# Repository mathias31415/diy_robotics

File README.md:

# diy_robotics

## Table of Contents
1. [Video of the results](#video)
2. [Overview](#overview)
3. [Possible improvements](#improvements)
4. [Part list](#partlist)
5. [Assembly-Videos by pfuscher666](#assemblyvideos)

<a name="video"/>

## Video of the results (in German)

This [YouTube video](https://www.youtube.com/watch?v=qf8R6U7XTOY) shows the results of our project work:

<a name="overview"/>

## Overview

This repo contains the results of a project work at the University of Applied Sciences Karlsruhe by **Robin Wolf, Hannes Bornemann and Mathias Fuhrer**. As part of the project work, the [Six-Axis Robot Arm WE-R2.4 from LoboCNC](https://www.printables.com/de/model/132260-we-r24-six-axis-robot-arm) was set up and a new gripper was developed.

The project was supervised by Gergely Sóti, Philipp Augenstein and Prof. Dr.-Ing. habil. Björn Hein.

The CAD files of the gripper and assembly instructions can be found in folder [diy_robotics_gripper_cad](https://github.com/mathias31415/diy_robotics/tree/main/diy_robotics_gripper_cad).

Two PCBs were designed for the electrical wiring: one PCB for the 6 axes and one PCB for the gripper. The KiCAD and Gerber files can be found in the folders [diy_robotics_arm_pcb](https://github.com/mathias31415/diy_robotics/tree/main/diy_robotics_arm_pcb) and [diy_robotics_gripper_pcb](https://github.com/mathias31415/diy_robotics/tree/main/diy_robotics_gripper_pcb).

To control the 6 axes and the gripper, ROS2 implementations were written that communicate via Wifi with an ESP32, from which the axes and the gripper are then moved. One ESP32 is responsible for the 6 axes, and the second ESP32 is responsible for the gripper.

The ROS2 packages are packaged in Docker containers so that they can be used by others without any problems. The repos of our ROS2 packages are linked in the folder [ROS-Packages](https://github.com/mathias31415/diy_robotics/tree/main/ROS-Packages). To just use our ROS application go to the repo [diy_robot_application](https://github.com/RobinWolf/diy_robot_application) and follow the HowTo. To understand our implementation you should read all readmes of our ROS repos 

The PC on which the ROS2 packages are executed must be connected to the same Wifi as the two ESP32s. The two ESP32s then receive messages from the PC via TCP-IP with the commands for the gripper and the 6-axes and then control the gripper and the axes accordingly. The VS-Code PlatformIO project folders for the ESP32 of the gripper and the axes can be found in the folders [diy_robotics_arm_esp32](https://github.com/mathias31415/diy_robotics/tree/main/diy_robotics_arm_esp32) and [diy_robotics_gripper_esp32](https://github.com/mathias31415/diy_robotics/tree/main/diy_robotics_gripper_esp32). Make sure to adapt the SSID and IP address as well as the password of your Wifi in the ``Configuration.h`` files.

The [hardwaretest_without_ROS](https://github.com/mathias31415/diy_robotics/tree/main/hardwaretest_without_ROS) folder contains additional programs to test the hardware without ROS via the Serial Monitor.

<a name="improvements"/>

## Possible improvements

- Conversion of the robot to metric screws
- Endstops or sensors to determine the position of the robot or to move it to a home position

<a name="partlist"/>

## Part list (as of March 2024)
The information serves as a guide only. Prices may change over time. It is also worth comparing other providers and manufacturers.
(Parts such as screws, filament and glue are not listed)

### 1. Robot-arm
| Index | Description | Quantity | Total price in € | Link |
| --- | --- | --- | --- | --- |
| 1 | Nema 17 Stepper-Motor 42Ncm | 3 | 15,55 | [Link](https://www.omc-stepperonline.com/de/3-stueck-e-serie-nema-17-bipolar-42-ncm-59-49-oz-in-1-5a-42x42x38mm-4-draehte-3-17he15-1504s) |
| 2 | Minibea PM35L-048 Stepper-Motor | 3 | 18,20 | [Link](https://www.ebay.de/itm/403845575203?_trkparms=amclksrc%3DITM%26aid%3D777008%26algo%3DPERSONAL.TOPIC%26ao%3D1%26asc%3D20230811123857%26meid%3D01b980ffd3f64d67a8210c3d282fd210%26pid%3D101770%26rk%3D1%26rkt%3D1%26itm%3D403845575203%26pmt%3D1%26noa%3D1%26pg%3D4375194%26algv%3DRecentlyViewedItemsV2%26brand%3DMarkenlos&_trksid=p4375194.c101770.m146925&_trkparms=parentrq%3Acd81805118b0a8cc93d6ff8cffffc172%7Cpageci%3Aa6388820-82dd-11ee-97f3-8e07020e1f61%7Ciid%3A1%7Cvlpname%3Avlp_homepage) |
| 3 | 6mm steel balls for bearings | 200 | 9,99 | [Link](https://www.amazon.de/dp/B01LPZ56ZC?psc=1&ref=ppx_yo2ov_dt_b_product_details ) |
| 4 | additional connection cable for motors 1,5m | 6 | 9,59 | [Link](https://www.amazon.de/Iverntech-Schrittmotor-Terminal-3D-Drucker-Stepper/dp/B08SQ35LRQ/ref=sr_1_6?crid=2UUMN13RQ0TTT&keywords=stepper%2Bmotor%2Bkabel&qid=1700576677&sprefix=stepper%2Bmotor%2B%2Caps%2C149&sr=8-6&th=1 ) |
| 5 | Power supply 24V 350W | 1 | 22,97 | [Link](https://www.omc-stepperonline.com/de/lrs-350-24-mean-well-350w-24vdc-14-6a-115-230vac-geschlossenes-schaltnetzteil-lrs-350-24) |
| 6 | Step-Down Converter 24V - 5V | 2 | 4,00 | [Link](https://www.amazon.de/Yizhet-Converter-Spannungsregler-Einstellbares-Abw%C3%A4Rtsmodul/dp/B0CKWYXD89/ref=sr_1_2_sspa?keywords=step+down+modul&qid=1699960183&sr=8-2-spons&sp_csd=d2lkZ2V0TmFtZT1zcF9hdGY&psc=1) |

### 2. Gripper
| Index | Description | Quantity | Total price in € | Link |
| --- | --- | --- | --- | --- |
| 1 | Servo SG90 Continuous Drive (Metal 360 Degree) | 2 | 9,00 | [Link](https://de.aliexpress.com/item/1005004550512467.html?spm=a2g0o.order_list.order_list_main.10.12875c5fjUap8p&gatewayAdapt=glo2deu) |

### 3. PCBs
The geber-files for the PCBs can be found in folders [diy_robotics_arm_pcb](https://github.com/mathias31415/diy_robotics/tree/main/diy_robotics_arm_pcb) and [diy_robotics_gripper_pcb](https://github.com/mathias31415/diy_robotics/tree/main/diy_robotics_gripper_pcb). With the geber-files, the PCBs can be ordered from any manufacturer. At JLCPCB we paid a total of just over €30 for 5 pieces of both PCBs.
The parts for assembling the PCBs are listed below. Note that some parts are required for both PCBs and are therefore listed twice. However, one set is often sufficient for both PCBs (e.g. for the pin headers). For components such as the ESP-32, it is cheaper to buy a set of two for both PCBs than to order two individual ESP-32s.

#### 3.1 Arm PCB
| Index | Description | Quantity | Total price in € | Link |
| --- | --- | --- | --- | --- |
| 1 | 0.96 Inch OLED Display SSD1306 | 1 | 1,78 | [Link](https://de.aliexpress.com/item/1005005970901119.html?spm=a2g0o.order_list.order_list_main.22.4a065c5ffRtZfv&gatewayAdapt=glo2deu) |
| 2 | ESP-32 | 1 | 10,00 | [Link](https://www.amazon.de/gp/aw/d/B074RG86SR/?_encoding=UTF8&pd_rd_plhdr=t&aaxitk=6a9e09b157f2b15a9cc364c1aba715aa&hsa_cr_id=4742246160502&qid=1699959775&sr=1-1-e0fa1fdd-d857-4087-adda-5bd576b25987&ref_=sbx_be_s_sparkle_mcd_asin_0_title&pd_rd_w=ee0VR&content-id=amzn1.sym.6f8b36f0-c2c9-44f2-97a8-5b151d2fc9c7%3Aamzn1.sym.6f8b36f0-c2c9-44f2-97a8-5b151d2fc9c7&pf_rd_p=6f8b36f0-c2c9-44f2-97a8-5b151d2fc9c7&pf_rd_r=0TBV9VYJCQK5QB253DBZ&pd_rd_wg=KZCjO&pd_rd_r=297525bc-30e7-47c9-996a-8a255adffee4)  |
| 3 | 2-Pin Screw Terminal 5mm | 3 | 4,56 for a set | [Link](https://de.aliexpress.com/item/1005005595075178.html?spm=a2g0o.order_list.order_list_main.17.4a065c5ffRtZfv&gatewayAdapt=glo2deu) |
| 4 | Pin Header 1x4 Pin Male 2,54mm | 6 |1,77 for male + female set | [Link](https://de.aliexpress.com/item/4000873858801.html?spm=a2g0o.detail.pcDetailTopMoreOtherSeller.2.e4a5600cBKuomq&gps-id=pcDetailTopMoreOtherSeller&scm=1007.40050.354490.0&scm_id=1007.40050.354490.0&scm-url=1007.40050.354490.0&pvid=c41c94ec-099f-42bf-a647-59697bc6a5d5&_t=gps-id:pcDetailTopMoreOtherSeller,scm-url:1007.40050.354490.0,pvid:c41c94ec-099f-42bf-a647-59697bc6a5d5,tpp_buckets:668%232846%238114%231999&pdp_npi=4%40dis%21EUR%211.77%211.77%21%21%211.89%211.89%21%4021038dfc17098923902746506e96e7%2110000010058190554%21rec%21DE%213958237401%21&utparam-url=scene%3ApcDetailTopMoreOtherSeller%7Cquery_from%3A) |
| 5 | Capacitor 25V 100uF | 6 | 1,78 for 50pcs | [Link](https://de.aliexpress.com/item/1005005945738204.html?spm=a2g0o.order_list.order_list_main.11.4a065c5ffRtZfv&gatewayAdapt=glo2deu) |
| 6 | DRV8825 Stepper Driver | 6 | 10,00 |  [Link](https://www.amazon.de/dp/B07YFS29W7?psc=1&ref=ppx_yo2ov_dt_b_product_details ) |
| 7 | 4-way DIP-Switch 2,54mm | 6 | 1,86 for 10pcs | [Link](https://de.aliexpress.com/item/1005006109195564.html?spm=a2g0o.order_list.order_list_main.10.4a065c5ffRtZfv&gatewayAdapt=glo2deu) |
| 8 | Female pin header 2,54mm for the display, ESP-32 and Stepper Drivers |  | 1,77 for male + female set | [Link](https://de.aliexpress.com/item/4000873858801.html?spm=a2g0o.detail.pcDetailTopMoreOtherSeller.2.e4a5600cBKuomq&gps-id=pcDetailTopMoreOtherSeller&scm=1007.40050.354490.0&scm_id=1007.40050.354490.0&scm-url=1007.40050.354490.0&pvid=c41c94ec-099f-42bf-a647-59697bc6a5d5&_t=gps-id:pcDetailTopMoreOtherSeller,scm-url:1007.40050.354490.0,pvid:c41c94ec-099f-42bf-a647-59697bc6a5d5,tpp_buckets:668%232846%238114%231999&pdp_npi=4%40dis%21EUR%211.77%211.77%21%21%211.89%211.89%21%4021038dfc17098923902746506e96e7%2110000010058190554%21rec%21DE%213958237401%21&utparam-url=scene%3ApcDetailTopMoreOtherSeller%7Cquery_from%3A) |

#### 3.2 Gripper PCB
| Index | Description | Quantity | Total price in € | Link |
| --- | --- | --- | --- | --- |
| 1 | 0.96 Inch OLED Display SSD1306 | 1 | 1,78 | [Link](https://de.aliexpress.com/item/1005005970901119.html?spm=a2g0o.order_list.order_list_main.22.4a065c5ffRtZfv&gatewayAdapt=glo2deu) |
| 2 | ESP-32 | 1 | 10,00 | [Link](https://www.amazon.de/gp/aw/d/B074RG86SR/?_encoding=UTF8&pd_rd_plhdr=t&aaxitk=6a9e09b157f2b15a9cc364c1aba715aa&hsa_cr_id=4742246160502&qid=1699959775&sr=1-1-e0fa1fdd-d857-4087-adda-5bd576b25987&ref_=sbx_be_s_sparkle_mcd_asin_0_title&pd_rd_w=ee0VR&content-id=amzn1.sym.6f8b36f0-c2c9-44f2-97a8-5b151d2fc9c7%3Aamzn1.sym.6f8b36f0-c2c9-44f2-97a8-5b151d2fc9c7&pf_rd_p=6f8b36f0-c2c9-44f2-97a8-5b151d2fc9c7&pf_rd_r=0TBV9VYJCQK5QB253DBZ&pd_rd_wg=KZCjO&pd_rd_r=297525bc-30e7-47c9-996a-8a255adffee4) |
| 3 | 2-Pin Screw Terminal 5mm | 2 | 4,56 for a set | [Link](https://de.aliexpress.com/item/1005005595075178.html?spm=a2g0o.order_list.order_list_main.17.4a065c5ffRtZfv&gatewayAdapt=glo2deu) |
| 4 | Pin Header 1x4 Pin Male 2,54mm | 1 | 1,77 for male + female set | [Link](https://de.aliexpress.com/item/4000873858801.html?spm=a2g0o.detail.pcDetailTopMoreOtherSeller.2.e4a5600cBKuomq&gps-id=pcDetailTopMoreOtherSeller&scm=1007.40050.354490.0&scm_id=1007.40050.354490.0&scm-url=1007.40050.354490.0&pvid=c41c94ec-099f-42bf-a647-59697bc6a5d5&_t=gps-id:pcDetailTopMoreOtherSeller,scm-url:1007.40050.354490.0,pvid:c41c94ec-099f-42bf-a647-59697bc6a5d5,tpp_buckets:668%232846%238114%231999&pdp_npi=4%40dis%21EUR%211.77%211.77%21%21%211.89%211.89%21%4021038dfc17098923902746506e96e7%2110000010058190554%21rec%21DE%213958237401%21&utparam-url=scene%3ApcDetailTopMoreOtherSeller%7Cquery_from%3A) |
| 5 | Female pin header 2,54mm for the display, ESP-32 and Stepper Drivers |  |1,77 for male + female set | [Link](https://de.aliexpress.com/item/4000873858801.html?spm=a2g0o.detail.pcDetailTopMoreOtherSeller.2.e4a5600cBKuomq&gps-id=pcDetailTopMoreOtherSeller&scm=1007.40050.354490.0&scm_id=1007.40050.354490.0&scm-url=1007.40050.354490.0&pvid=c41c94ec-099f-42bf-a647-59697bc6a5d5&_t=gps-id:pcDetailTopMoreOtherSeller,scm-url:1007.40050.354490.0,pvid:c41c94ec-099f-42bf-a647-59697bc6a5d5,tpp_buckets:668%232846%238114%231999&pdp_npi=4%40dis%21EUR%211.77%211.77%21%21%211.89%211.89%21%4021038dfc17098923902746506e96e7%2110000010058190554%21rec%21DE%213958237401%21&utparam-url=scene%3ApcDetailTopMoreOtherSeller%7Cquery_from%3A) |

<a name="assemblyvideos"/>

## Assembly-Videos by pfuscher666

[Pfuscher666](https://www.youtube.com/@pfuscher666) made a nice assembly video series on YouTube using our Github repo. If you want to recreate the robot, we recommend checking out his [playlist](https://youtube.com/playlist?list=PLlPSE-8AfOheRNZ__qo-JLWLydIsqo4Fw&si=UZEIlQIDYb_gISjW).

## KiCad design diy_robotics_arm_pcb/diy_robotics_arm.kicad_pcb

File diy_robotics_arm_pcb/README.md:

# diy_robotics_arm_pcb

① 0.96 Inch OLED Display SSD1306 (1 pcs.) 

② ESP-32 (1 pcs.)

③ 2-Pin Screw Terminal 5mm (3 pcs.)

④ Pin Header 1x4 Pin Male 2,54mm (6 pcs.)

⑤ Capacitor 25V 100uF (6 pcs.)

⑥ DRV8825 Stepper Driver (6 pcs.)

⑦ 4-way DIP-Switch 2,54mm (6 pcs.)

(①, ② and  ⑥ are plugged into female pin header 2,54mm)

5V for the ESP32 power supply must be connected to the "VCC_ESP32" screw terminal. 24V for the servo stepper power supply must be connected to the "VCC_Stepper" (on the picture incorrectly "VCC_Servo") screw terminal. The steppers of axes 1 - 6 are connected to the pin header "Axis 1-6". An external enable switch can be connected to the "Enable" screw terminal. This allows the axes to be switched off independently of the software. If no switch is to be used, the contacts can be short-circuited.

### Schamatic

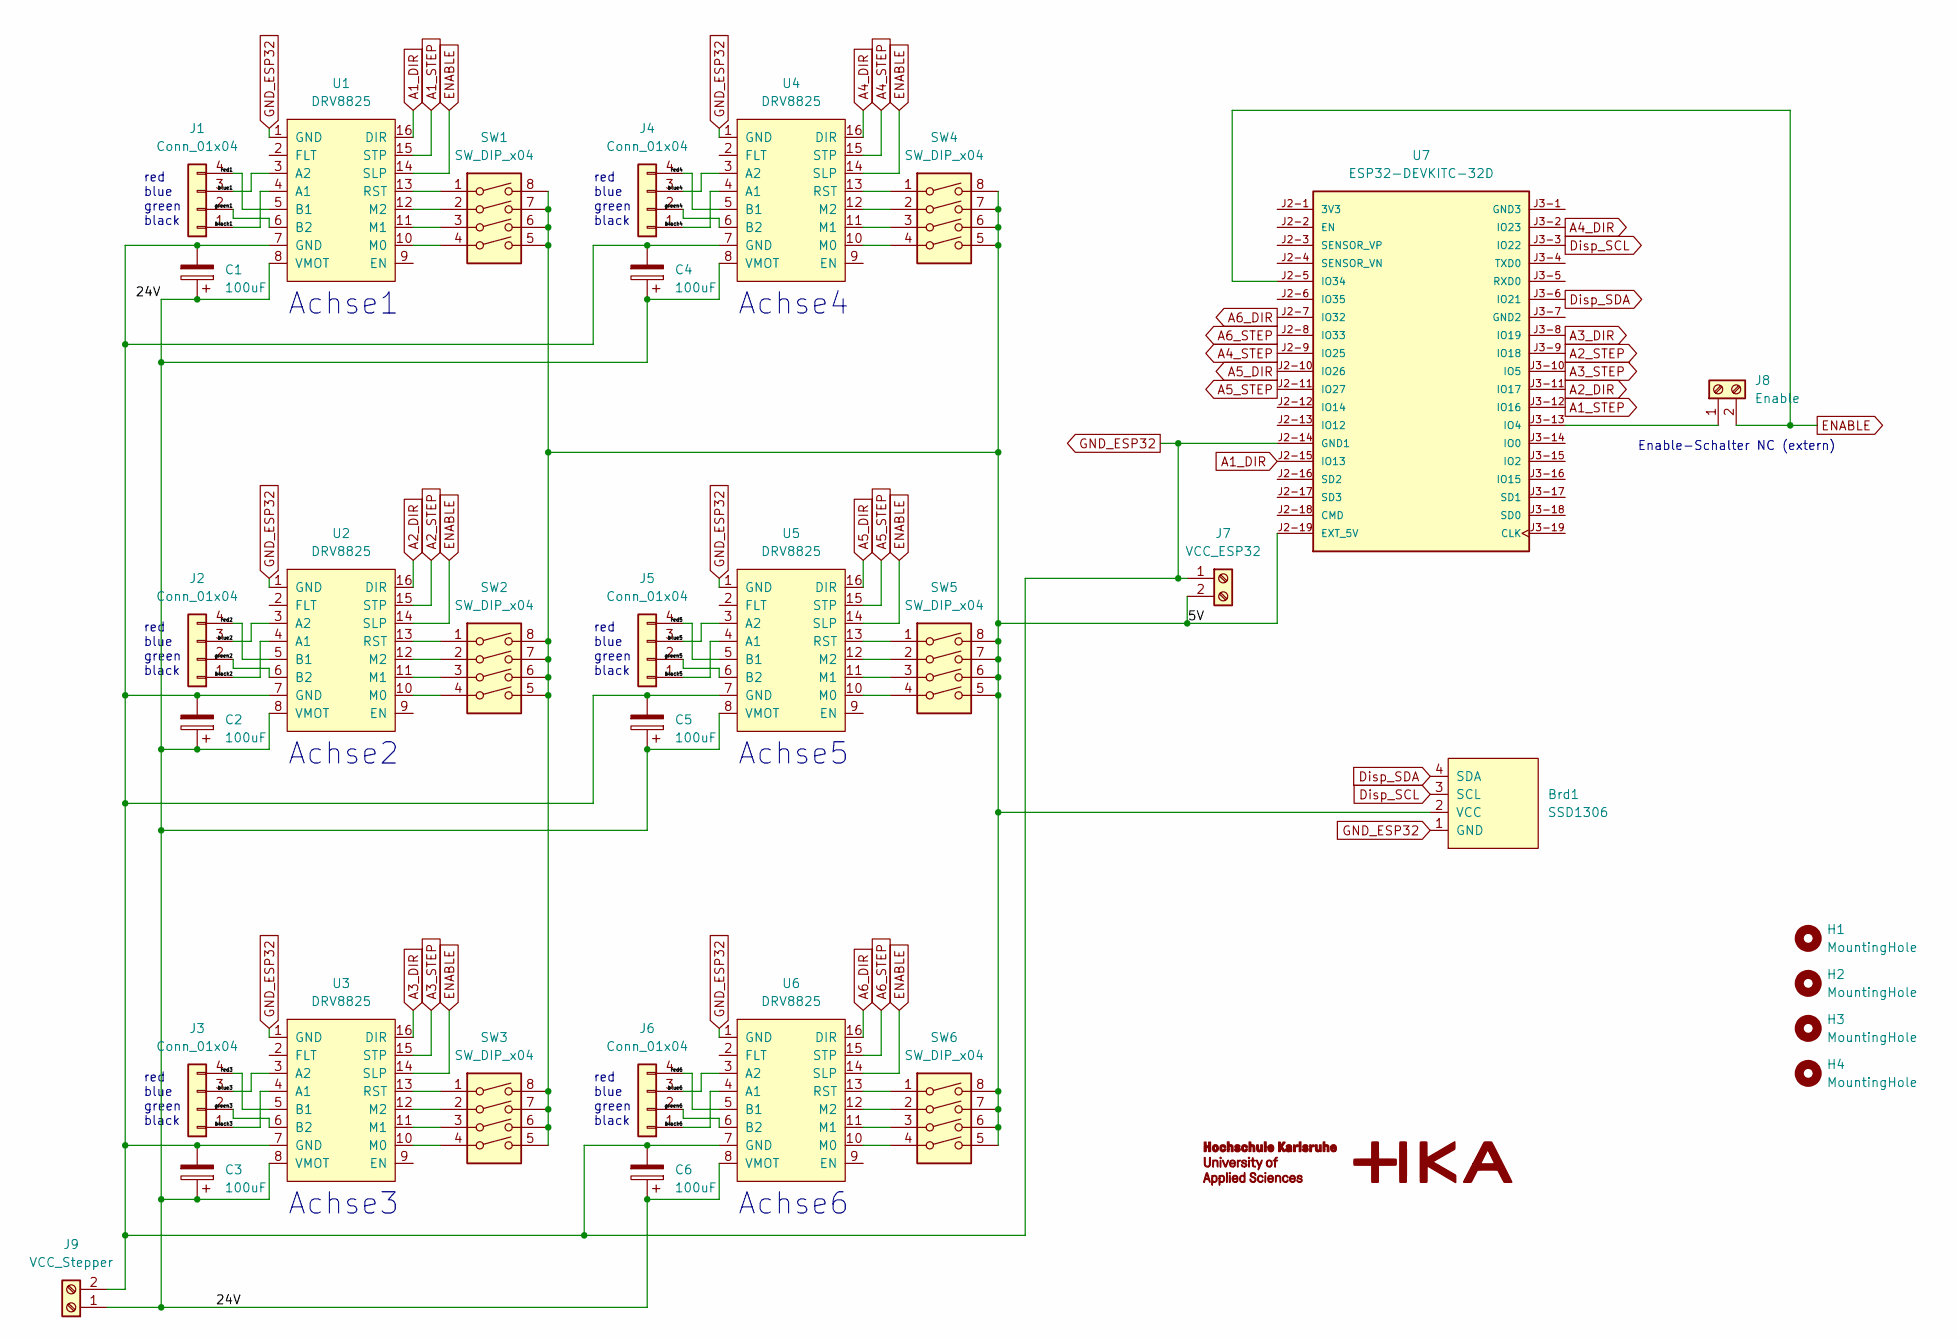
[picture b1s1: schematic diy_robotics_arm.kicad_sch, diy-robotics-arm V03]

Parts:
Brd1: SSD1306; 128x64OLED
C1, C2, C3, C4, C5, C6: 100uF; CP_Radial_D5.0mm_P2.00mm
H1, H2, H3, H4: MountingHole; MountingHole_3.2mm_M3_DIN965_Pad
J1, J2, J3, J4, J5, J6: Conn_01x04; PinHeader_1x04_P2.54mm_Vertical
J7: VCC_ESP32; TerminalBlock_Phoenix_MKDS-1,5-2_1x02_P5.00mm_Horizontal
J8: Enable; TerminalBlock_Phoenix_MKDS-1,5-2_1x02_P5.00mm_Horizontal
J9: VCC_Stepper; TerminalBlock_Phoenix_MKDS-1,5-2_1x02_P5.00mm_Horizontal
SW1, SW2, SW3, SW4, SW5, SW6: SW_DIP_x04; SW_DIP_SPSTx04_Slide_9.78x12.34mm_W7.62mm_P2.54mm
U1, U2, U3, U4, U5, U6: DRV8825; DRV8825_Breakout_15.2x20.3mm
U7: ESP32-DEVKITC-32D; MODULE_ESP32-DEVKITC-32D; PARTREV V4

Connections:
/5V: Brd1.2 (VCC), J7.2, SW1.5, SW1.6, SW1.7, SW1.8, SW2.5, SW2.6, SW2.7, SW2.8, SW3.5, SW3.6, SW3.7, SW3.8, SW4.5, SW4.6, SW4.7, SW4.8, SW5.5, SW5.6, SW5.7, SW5.8, SW6.5, SW6.6, SW6.7, SW6.8, U7.J2-19 (EXT_5V)
/24V: C1.1, C2.1, C3.1, C4.1, C5.1, C6.1, J9.1, U1.8 (VMOT), U2.8 (VMOT), U3.8 (VMOT), U4.8 (VMOT), U5.8 (VMOT), U6.8 (VMOT)
/black1: J1.1, U1.4 (A1)
/black2: J2.1, U2.4 (A1)
/black3: J3.1, U3.4 (A1)
/black4: J4.1, U4.4 (A1)
/black5: J5.1, U5.4 (A1)
/black6: J6.1, U6.4 (A1)
/blue1: J1.3, U1.3 (A2)
/blue2: J2.3, U2.3 (A2)
/blue3: J3.3, U3.3 (A2)
/blue4: J4.3, U4.3 (A2)
/blue5: J5.3, U5.3 (A2)
/blue6: J6.3, U6.3 (A2)
/green1: J1.2, U1.6 (B2)
/green2: J2.2, U2.6 (B2)
/green3: J3.2, U3.6 (B2)
/green4: J4.2, U4.6 (B2)
/green5: J5.2, U5.6 (B2)
/green6: J6.2, U6.6 (B2)
/red1: J1.4, U1.5 (B1)
/red2: J2.4, U2.5 (B1)
/red3: J3.4, U3.5 (B1)
/red4: J4.4, U4.5 (B1)
/red5: J5.4, U5.5 (B1)
/red6: J6.4, U6.5 (B1)
A1_DIR: U1.16 (DIR), U7.J2-15 (IO13)
A1_STEP: U1.15 (STP), U7.J3-12 (IO16)
A2_DIR: U2.16 (DIR), U7.J3-11 (IO17)
A2_STEP: U2.15 (STP), U7.J3-9 (IO18)
A3_DIR: U3.16 (DIR), U7.J3-8 (IO19)
A3_STEP: U3.15 (STP), U7.J3-10 (IO5)
A4_DIR: U4.16 (DIR), U7.J3-2 (IO23)
A4_STEP: U4.15 (STP), U7.J2-9 (IO25)
A5_DIR: U5.16 (DIR), U7.J2-10 (IO26)
A5_STEP: U5.15 (STP), U7.J2-11 (IO27)
A6_DIR: U6.16 (DIR), U7.J2-7 (IO32)
A6_STEP: U6.15 (STP), U7.J2-8 (IO33)
Disp_SCL: Brd1.3 (SCL), U7.J3-3 (IO22)
Disp_SDA: Brd1.4 (SDA), U7.J3-6 (IO21)
ENABLE: J8.2, U1.14 (SLP), U2.14 (SLP), U3.14 (SLP), U4.14 (SLP), U5.14 (SLP), U6.14 (SLP), U7.J2-5 (IO34)
GND_ESP32: Brd1.1 (GND), C1.2, C2.2, C3.2, C4.2, C5.2, C6.2, J7.1, J9.2, U1.1 (GND), U1.7 (GND), U2.1 (GND), U2.7 (GND), U3.1 (GND), U3.7 (GND), U4.1 (GND), U4.7 (GND), U5.1 (GND), U5.7 (GND), U6.1 (GND), U6.7 (GND), U7.J2-14 (GND1)
unnamed: J8.1, U7.J3-13 (IO4)
unnamed: SW1.4, U1.10 (M0)
unnamed: SW1.3, U1.11 (M1)
unnamed: SW1.2, U1.12 (M2)
unnamed: SW1.1, U1.13 (RST)
unnamed: SW2.4, U2.10 (M0)
unnamed: SW2.3, U2.11 (M1)
unnamed: SW2.2, U2.12 (M2)
unnamed: SW2.1, U2.13 (RST)
unnamed: SW3.4, U3.10 (M0)
unnamed: SW3.3, U3.11 (M1)
unnamed: SW3.2, U3.12 (M2)
unnamed: SW3.1, U3.13 (RST)
unnamed: SW4.4, U4.10 (M0)
unnamed: SW4.3, U4.11 (M1)
unnamed: SW4.2, U4.12 (M2)
unnamed: SW4.1, U4.13 (RST)
unnamed: SW5.4, U5.10 (M0)
unnamed: SW5.3, U5.11 (M1)
unnamed: SW5.2, U5.12 (M2)
unnamed: SW5.1, U5.13 (RST)
unnamed: SW6.4, U6.10 (M0)
unnamed: SW6.3, U6.11 (M1)
unnamed: SW6.2, U6.12 (M2)
unnamed: SW6.1, U6.13 (RST)

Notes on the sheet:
red blue green black
Achse6
Achse3
Achse4
Achse1
Enable-Schalter NC (extern)
Achse2
Achse5

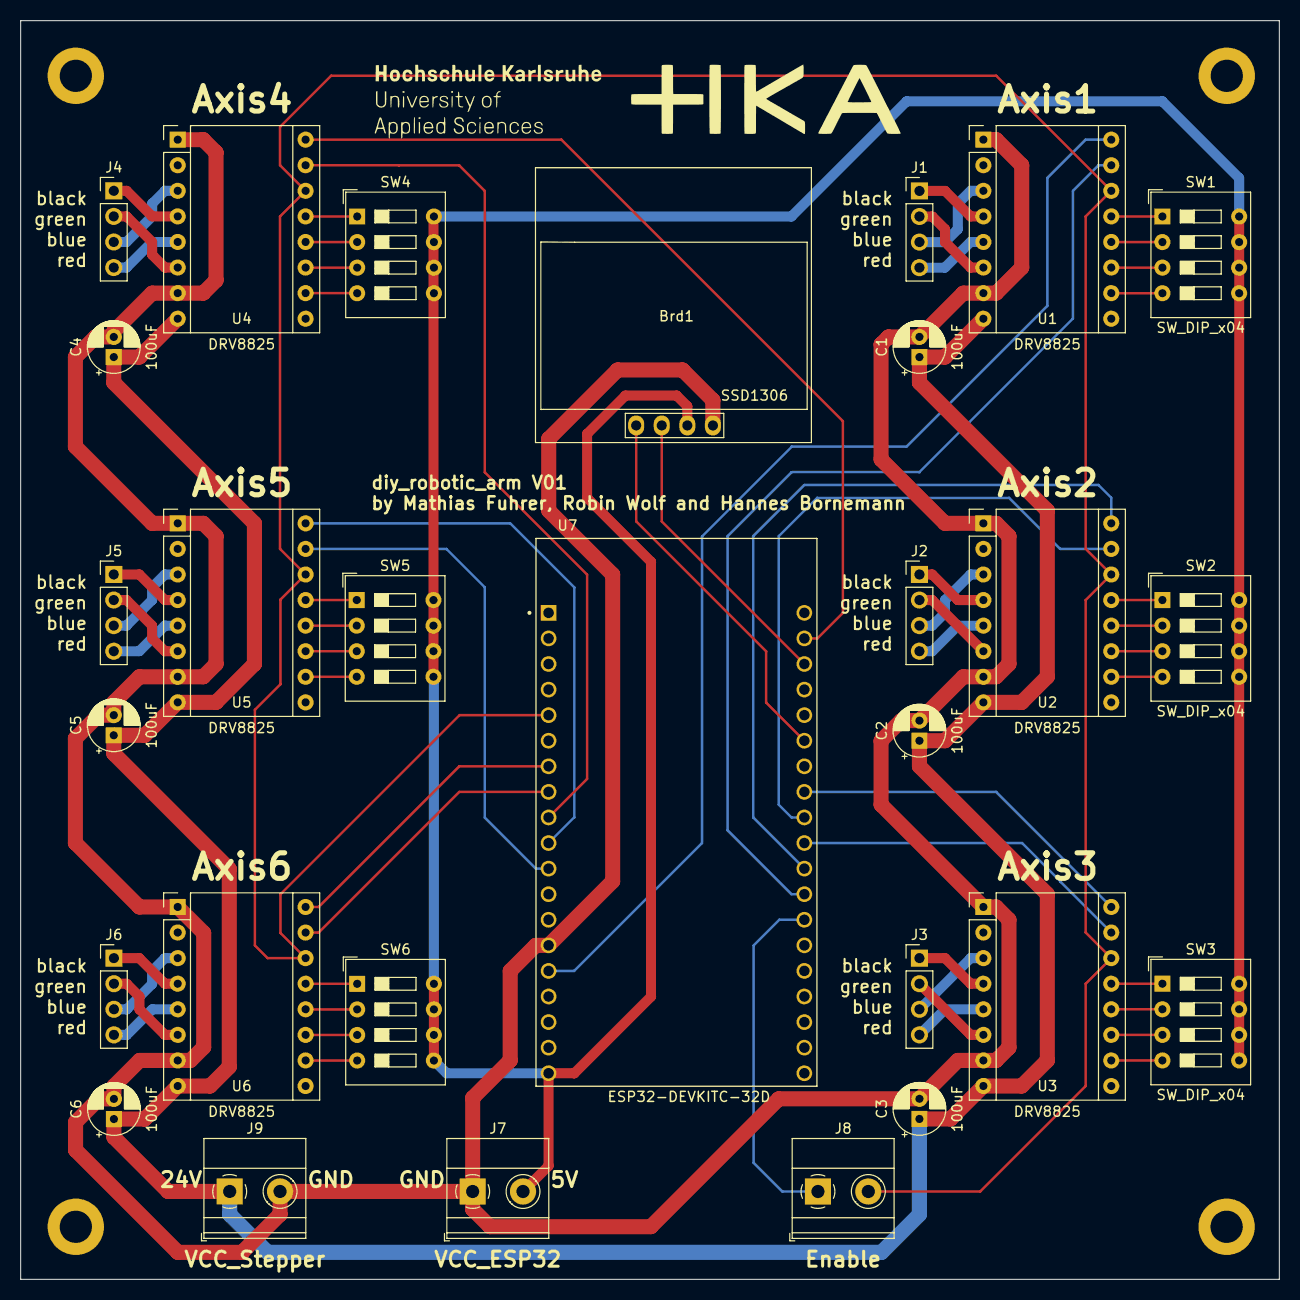
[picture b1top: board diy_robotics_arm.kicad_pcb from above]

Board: 2 copper layers, 125.0 x 125.0 mm, 33 parts (0 on the bottom side), 67 nets.

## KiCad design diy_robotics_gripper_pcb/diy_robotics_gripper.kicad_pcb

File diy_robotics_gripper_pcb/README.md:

# diy_robotics_gripper_pcb

① 0.96 Inch OLED Display SSD1306 (1 pcs.) 

② ESP-32 (1 pcs.)

③ 2-Pin Screw Terminal 5mm (2 pcs.)

④ Pin Header 1x4 Male 2,54mm (1 pcs.)

⑤ Pin Header Female 2,54mm

(① and ② are plugged into female pin header 2,54mm)

5V for the ESP32 power supply must be connected to the "VCC_ESP32" screw terminal. The power supply for the servo must be connected to the "VCC_Servo" screw terminal (6V). The servos are connected to the pin header "gripper servos".

### Schamatic

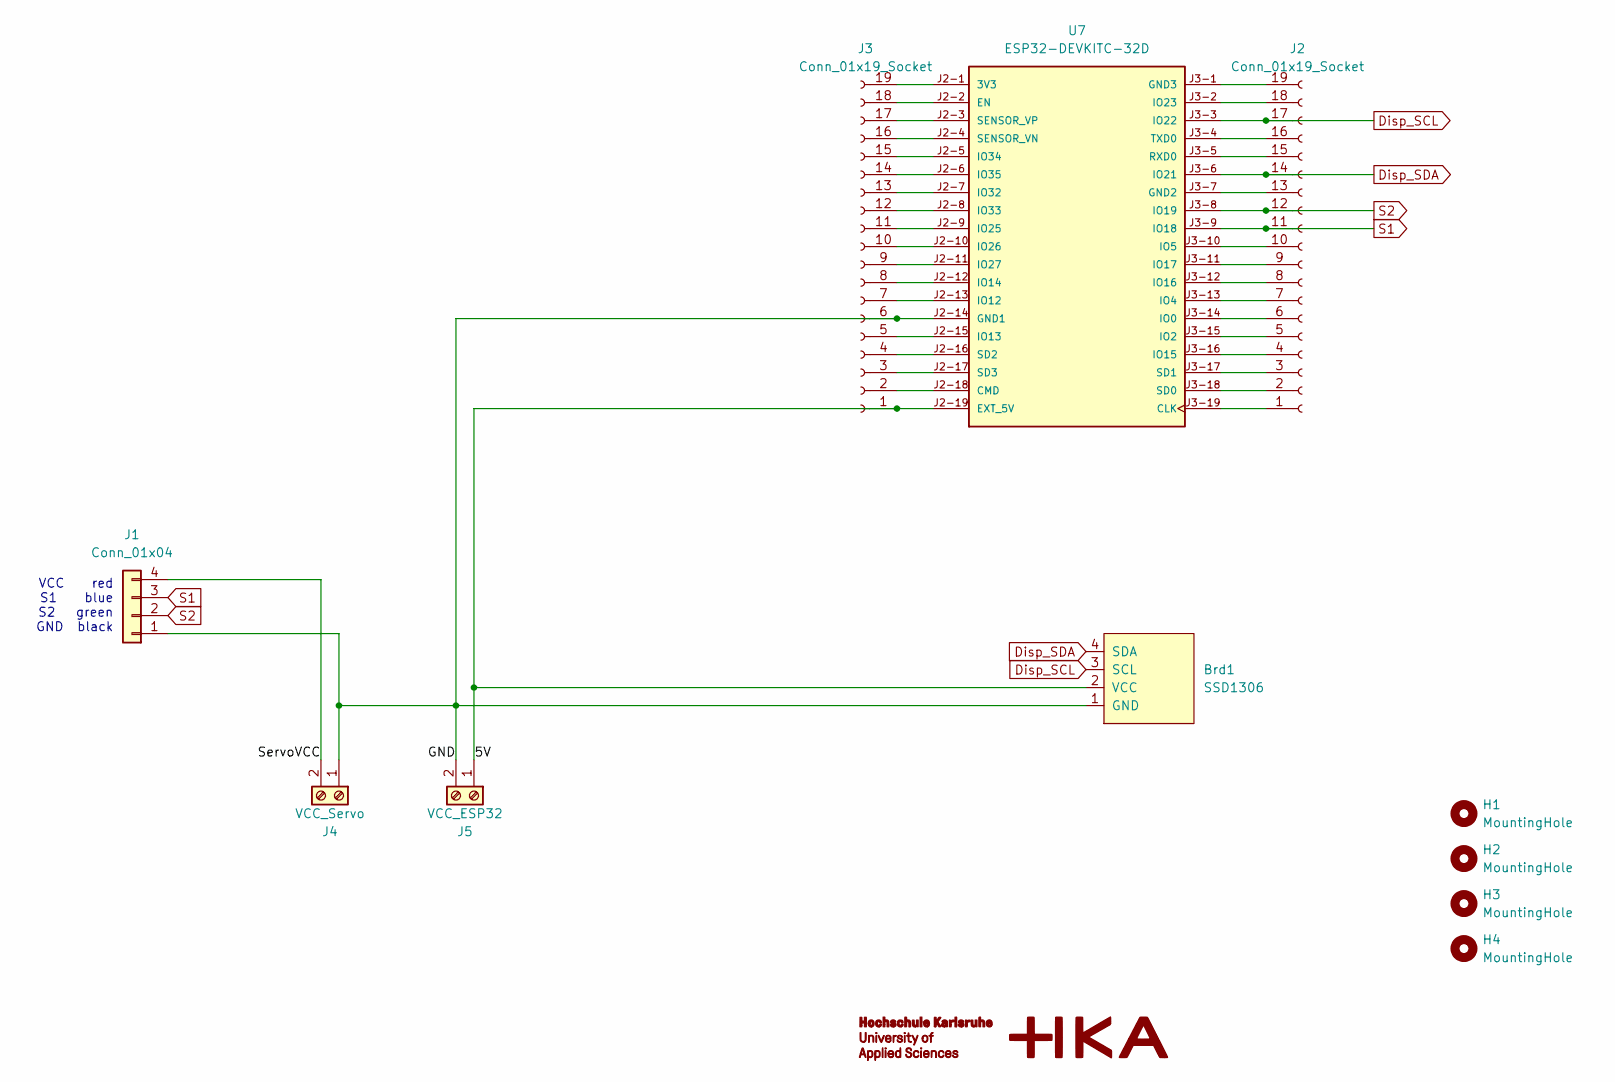
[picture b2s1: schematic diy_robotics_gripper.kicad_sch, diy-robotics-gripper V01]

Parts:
Brd1: SSD1306; 128x64OLED
H1, H2, H3, H4: MountingHole; MountingHole_3.2mm_M3_DIN965_Pad
J1: Conn_01x04; PinHeader_1x04_P2.54mm_Vertical
J2, J3: Conn_01x19_Socket; PinSocket_1x19_P2.54mm_Vertical
J4: VCC_Servo; TerminalBlock_Phoenix_MKDS-1,5-2_1x02_P5.00mm_Horizontal
J5: VCC_ESP32; TerminalBlock_Phoenix_MKDS-1,5-2_1x02_P5.00mm_Horizontal
U7: ESP32-DEVKITC-32D; MODULE_ESP32-DEVKITC-32D; PARTREV V4

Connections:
/5V: Brd1.2 (VCC), J3.1, J5.1, U7.J2-19 (EXT_5V)
/GND: Brd1.1 (GND), J1.1, J3.6, J4.1, J5.2, U7.J2-14 (GND1)
/ServoVCC: J1.4, J4.2
Disp_SCL: Brd1.3 (SCL), J2.17, U7.J3-3 (IO22)
Disp_SDA: Brd1.4 (SDA), J2.14, U7.J3-6 (IO21)
unnamed: J2.1, U7.J3-19 (CLK)
unnamed: J2.2, U7.J3-18 (SD0)
unnamed: J2.3, U7.J3-17 (SD1)
unnamed: J2.4, U7.J3-16 (IO15)
unnamed: J2.5, U7.J3-15 (IO2)
unnamed: J2.6, U7.J3-14 (IO0)
unnamed: J2.7, U7.J3-13 (IO4)
unnamed: J2.8, U7.J3-12 (IO16)
unnamed: J2.9, U7.J3-11 (IO17)
unnamed: J2.10, U7.J3-10 (IO5)
unnamed: J2.13, U7.J3-7 (GND2)
unnamed: J2.15, U7.J3-5 (RXD0)
unnamed: J2.16, U7.J3-4 (TXD0)
unnamed: J2.18, U7.J3-2 (IO23)
unnamed: J2.19, U7.J3-1 (GND3)
unnamed: J3.2, U7.J2-18 (CMD)
unnamed: J3.3, U7.J2-17 (SD3)
unnamed: J3.4, U7.J2-16 (SD2)
unnamed: J3.5, U7.J2-15 (IO13)
unnamed: J3.7, U7.J2-13 (IO12)
unnamed: J3.8, U7.J2-12 (IO14)
unnamed: J3.9, U7.J2-11 (IO27)
unnamed: J3.10, U7.J2-10 (IO26)
unnamed: J3.11, U7.J2-9 (IO25)
unnamed: J3.12, U7.J2-8 (IO33)
unnamed: J3.13, U7.J2-7 (IO32)
unnamed: J3.14, U7.J2-6 (IO35)
unnamed: J3.15, U7.J2-5 (IO34)
unnamed: J3.16, U7.J2-4 (SENSOR_VN)
unnamed: J3.17, U7.J2-3 (SENSOR_VP)
unnamed: J3.18, U7.J2-2 (EN)
unnamed: J3.19, U7.J2-1 (3V3)
S1: J1.3, J2.11, U7.J3-9 (IO18)
S2: J1.2, J2.12, U7.J3-8 (IO19)

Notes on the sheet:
VCC red S1 blue S2 green GND black

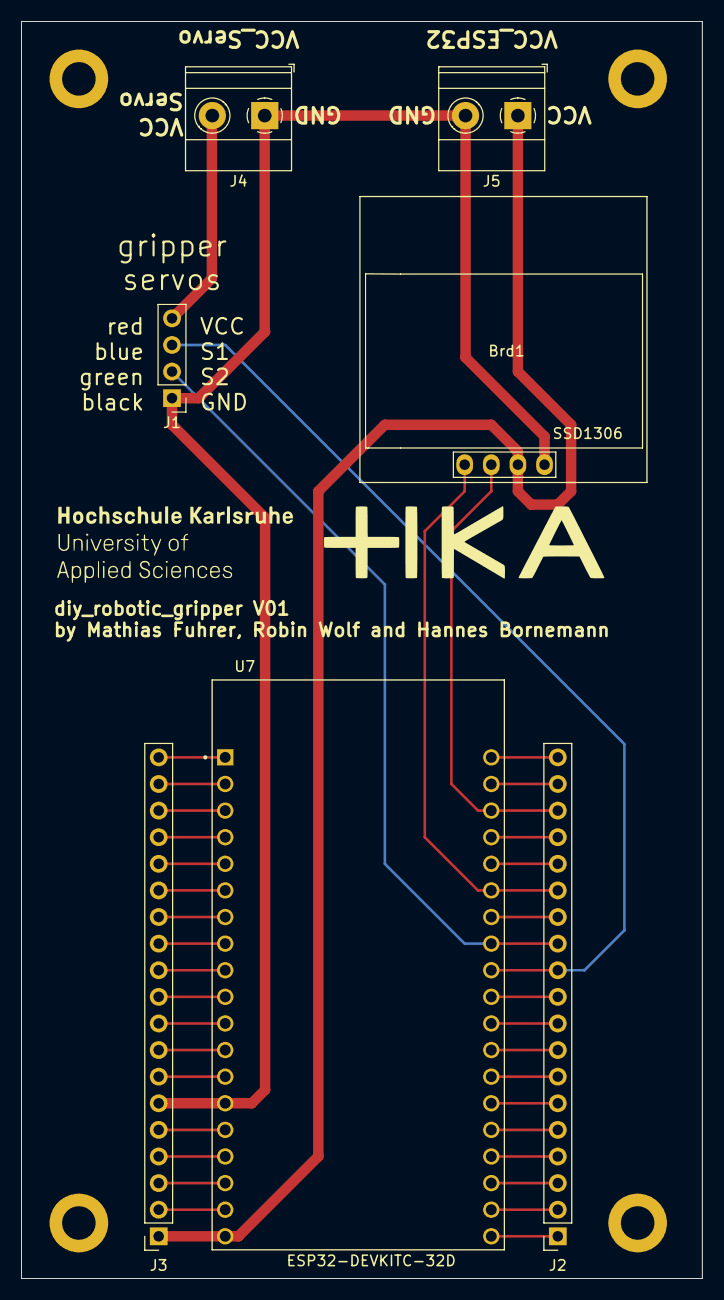
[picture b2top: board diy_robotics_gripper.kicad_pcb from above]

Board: 2 copper layers, 65.0 x 120.0 mm, 11 parts (0 on the bottom side), 39 nets.

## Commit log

2024-02-11 added overview and possible improvements to README
2024-02-11 added diy_robotics_arm_esp32
2024-02-11 added diy_robotics_gripper_esp32
2024-02-11 added diy_robotics_gripper_cad
2024-02-11 Readme
2024-02-11 added pcb folders
2024-02-11 added links to readme
2024-02-11 readme formatted
2024-02-11 path of images corrected
2024-02-11 removed test picture
2024-02-11 changed relative imgPath
2024-02-11 added gripper img to readme
2024-02-11 added link to robot
2024-02-11 added readme for diy_robotics_arm_esp32
2024-02-11 added readme for diy_robotics_gripper_esp32
2024-02-11 added readmes for pcb folders
2024-02-12 img of pcbs to readme
2024-02-12 modified readmes for pcbs
2024-02-12 cad files and partlist in readme
2024-02-12 added mounting instruction
2024-02-12 geber files in zip
2024-02-12 VCC_Servo lable corrected to VCC_Stepper
2024-02-12 kabelführung verbessert
2024-02-13 modified laufschiene
2024-02-13 added code for hardwaretest without ros
2024-02-13 added readme for test_without_ros
2024-02-18 description_packages.png
2024-02-18 Rename image.png to description_packages.png
2024-02-18 created ros folder
2024-02-18 add arm description submodule
2024-02-18 add gripper description submodule
2024-02-18 removed arm submodule, wrong repo
2024-02-18 add description submodules
2024-02-22 renamed readme
2024-02-22 Spelling mistake corrected
2024-02-23 added image to readme
2024-02-23 changed communicaton img
2024-02-23 add arm-driver submodule
2024-02-23 add gripper driver submodule
2024-02-23 add application submodule
2024-02-23 add moveit submodule
2024-02-27 CAD FinRay_Finger added
2024-03-05 Update README.md
    formatting
2024-03-06 Update CONCEPT.md
    drive concept written
2024-03-06 upload
2024-03-06 Update CONCEPT.md
    finish
2024-03-06 Update CONCEPT.md
    update
2024-03-07 added img of the robot to readme
2024-03-08 edited readme arm pcb
2024-03-08 edited gripper pcb readme
2024-03-08 added partlist to main readme
2024-03-08 edited readme
2024-03-08 Update README.md
    change servo specification
2024-03-12 updated submodules to latest commit
2024-03-12 added schematics to pcb readmes
2024-03-16 updated submodule
2024-03-26 Video of the results to readme
2024-03-26 Table of Contents to readme
2024-05-08 removed serial prints
2024-05-08 modified onDataReceived method to disable axis when not moving (to prevent overheating)
2024-05-26 fixed code to stop the axis motion in rviz and on display when robot ist stoped via hardware enable switch
2024-07-01 added video preview image
2024-07-01 added video preview to readme
2024-07-01 added image VideoPreviewPfuscher666.png
2024-07-01 added preview of assembly video by pfuscher666
